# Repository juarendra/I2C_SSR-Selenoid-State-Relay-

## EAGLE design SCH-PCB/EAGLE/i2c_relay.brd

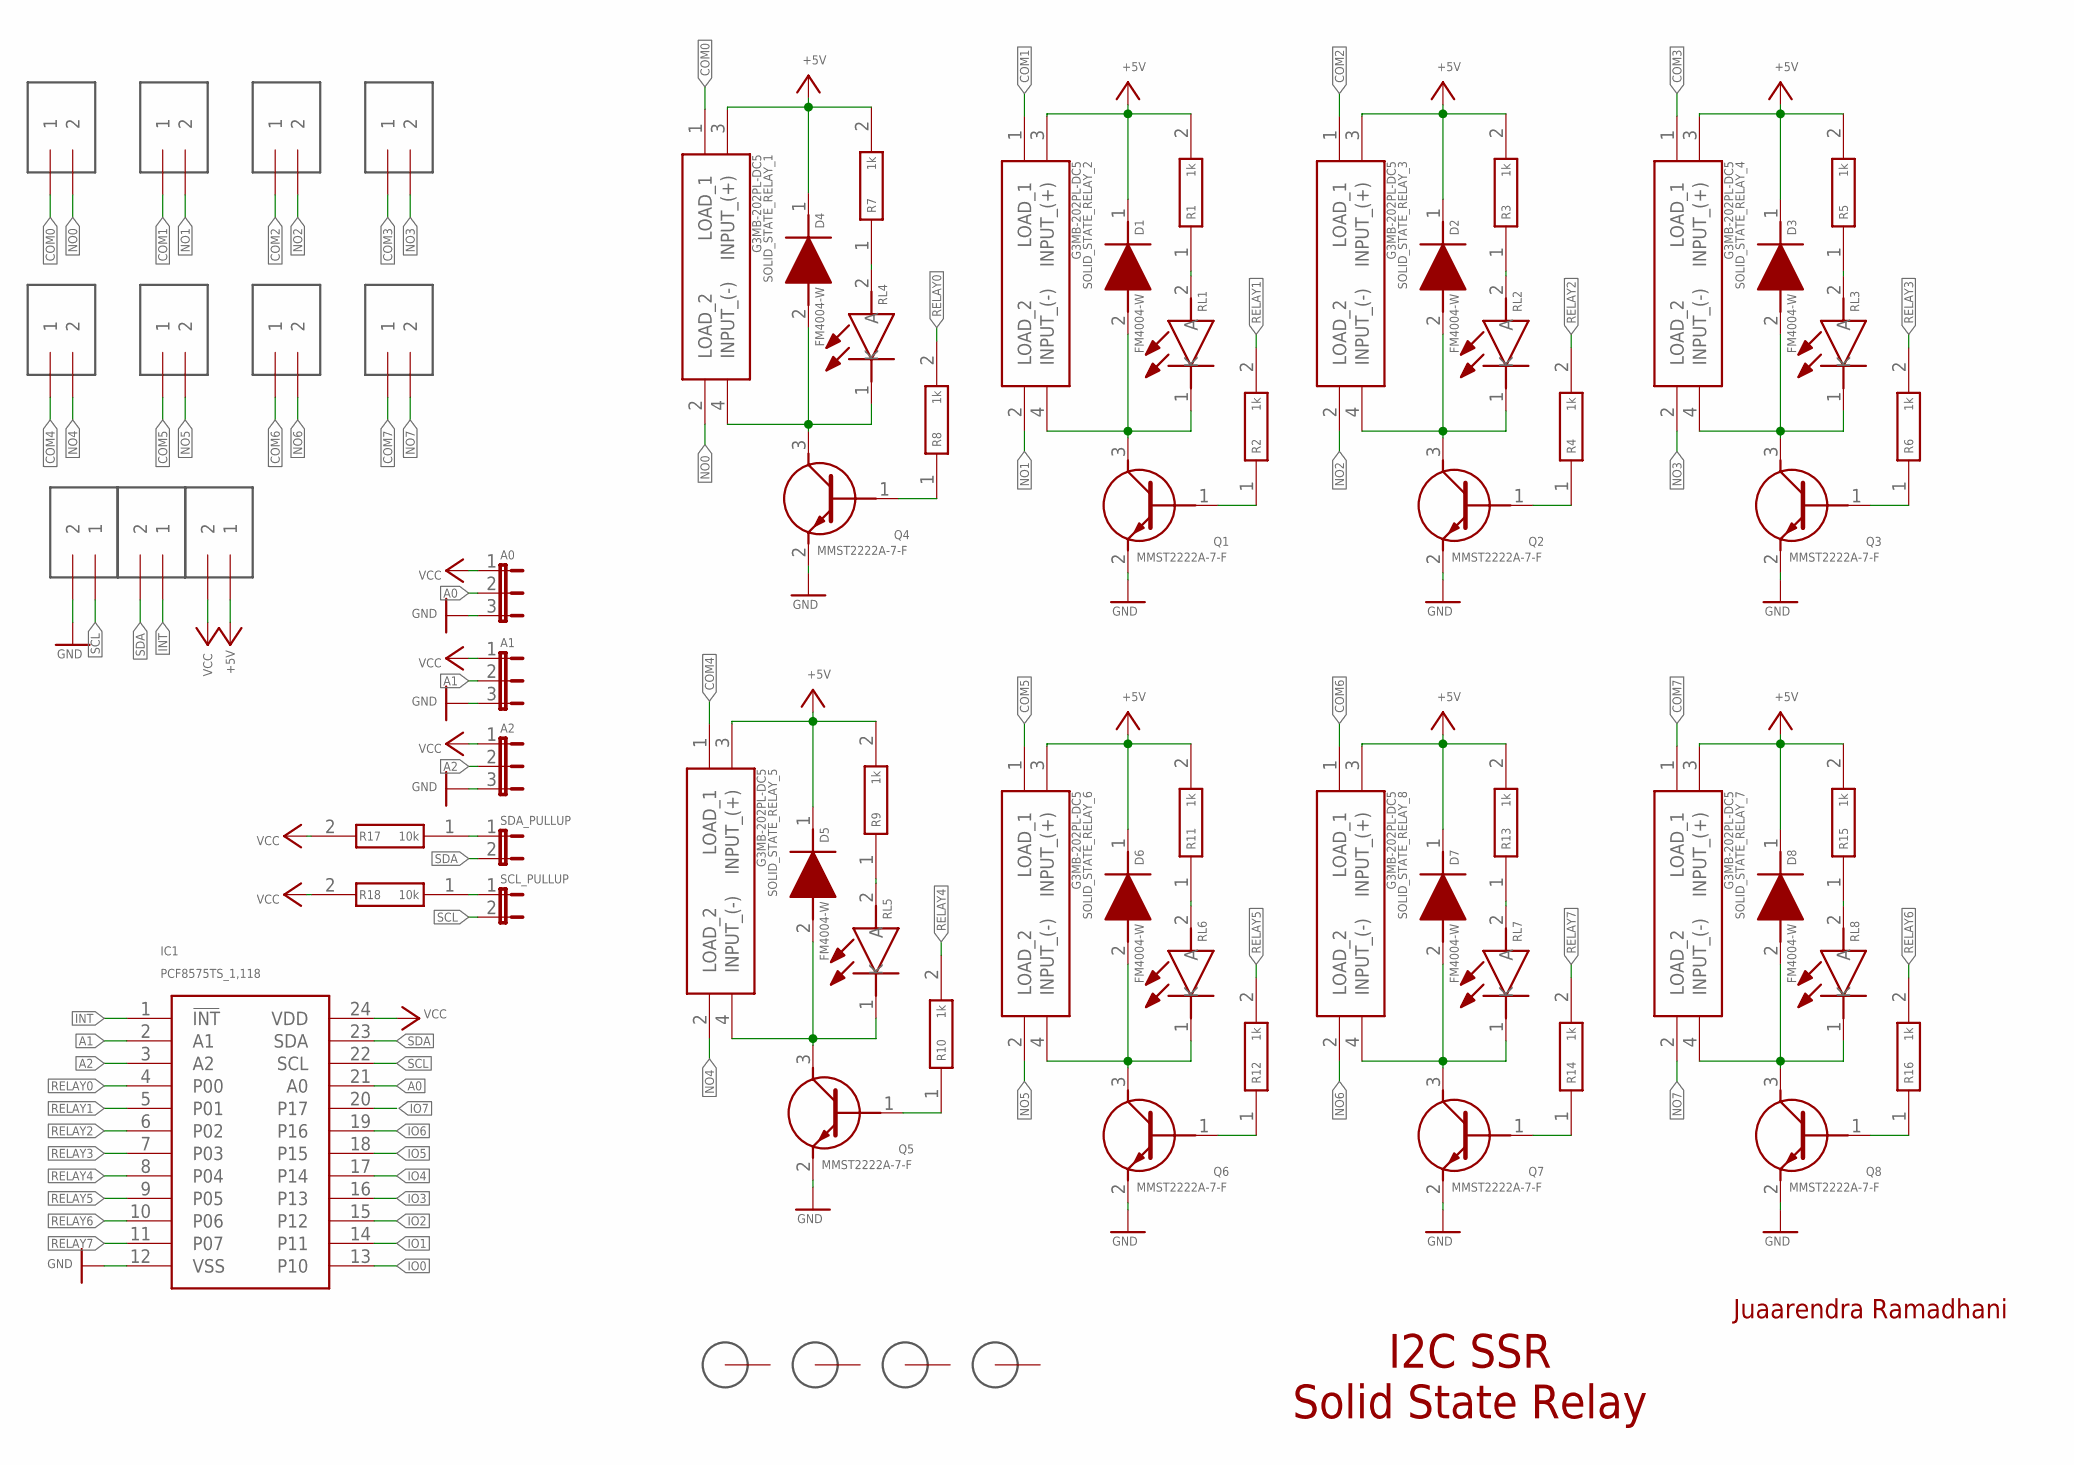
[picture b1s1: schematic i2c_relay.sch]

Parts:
A0, A1, A2: JP2E; JP2
D1, D2, D3, D4, D5, D6, D7, D8: FM4004-W; DIONM5025X231N
H1, H2, H3, H4: 3MM_HOLE
IC1: PCF8575TS_1,118; SOP65P775X200-24N
Q1, Q2, Q3, Q4, Q5, Q6, Q7, Q8: MMST2222A-7-F; SOT65P210X110-3N
R1, R2, R3, R4, R5, R6, R7, R8, R9, R10, R11, R12, R13, R14, R15, R16: 1k; ERA3AEB101V
R17, R18: 10k; RESC1608X55N
RL1, RL2, RL3, RL4, RL5, RL6, RL7, RL8: 150080SS75000; LEDC2012X80N
SCL_PULLUP: JP1E; JP1
SDA_PULLUP: JP1E; JP1
SOLID_STATE_RELAY_1, SOLID_STATE_RELAY_2, SOLID_STATE_RELAY_3, SOLID_STATE_RELAY_4, SOLID_STATE_RELAY_5, SOLID_STATE_RELAY_6, SOLID_STATE_RELAY_7, SOLID_STATE_RELAY_8: G3MB-202PL-DC5; G3MB202PLDC5
U$1, U$2, U$3, U$4, U$5, U$6, U$7, U$8, U$9, U$10, U$11: TERMINAL_2P; KF301-2P

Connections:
+5V: D1.1 (K), D2.1 (K), D3.1 (K), D4.1 (K), D5.1 (K), D6.1 (K), D7.1 (K), D8.1 (K), R1.2, R3.2, R5.2, R7.2, R9.2, R11.2, R13.2, R15.2, SOLID_STATE_RELAY_1.3 (INPUT_(+)), SOLID_STATE_RELAY_2.3 (INPUT_(+)), SOLID_STATE_RELAY_3.3 (INPUT_(+)), SOLID_STATE_RELAY_4.3 (INPUT_(+)), SOLID_STATE_RELAY_5.3 (INPUT_(+)), SOLID_STATE_RELAY_6.3 (INPUT_(+)), SOLID_STATE_RELAY_7.3 (INPUT_(+)), SOLID_STATE_RELAY_8.3 (INPUT_(+)), U$11.1
A0: A0.2, IC1.21 (A0)
A1: A1.2, IC1.2 (A1)
A2: A2.2, IC1.3 (A2)
COM0: SOLID_STATE_RELAY_1.1 (LOAD_1), U$1.1
COM1: SOLID_STATE_RELAY_2.1 (LOAD_1), U$2.1
COM2: SOLID_STATE_RELAY_3.1 (LOAD_1), U$3.1
COM3: SOLID_STATE_RELAY_4.1 (LOAD_1), U$4.1
COM4: SOLID_STATE_RELAY_5.1 (LOAD_1), U$5.1
COM5: SOLID_STATE_RELAY_6.1 (LOAD_1), U$6.1
COM6: SOLID_STATE_RELAY_8.1 (LOAD_1), U$7.1
COM7: SOLID_STATE_RELAY_7.1 (LOAD_1), U$8.1
GND: A0.3, A1.3, A2.3, IC1.12 (VSS), Q1.2 (E), Q2.2 (E), Q3.2 (E), Q4.2 (E), Q5.2 (E), Q6.2 (E), Q7.2 (E), Q8.2 (E), U$9.2
INT: IC1.1 (!INT), U$10.1
IO0: IC1.13 (P10)
IO1: IC1.14 (P11)
IO2: IC1.15 (P12)
IO3: IC1.16 (P13)
IO4: IC1.17 (P14)
IO5: IC1.18 (P15)
IO6: IC1.19 (P16)
IO7: IC1.20 (P17)
unnamed: R1.1, RL1.2 (A)
unnamed: D1.2 (A), Q1.3 (C), RL1.1 (K), SOLID_STATE_RELAY_2.4 (INPUT_(-))
unnamed: Q1.1 (B), R2.1
unnamed: R3.1, RL2.2 (A)
unnamed: D2.2 (A), Q2.3 (C), RL2.1 (K), SOLID_STATE_RELAY_3.4 (INPUT_(-))
unnamed: Q2.1 (B), R4.1
unnamed: R5.1, RL3.2 (A)
unnamed: D3.2 (A), Q3.3 (C), RL3.1 (K), SOLID_STATE_RELAY_4.4 (INPUT_(-))
unnamed: Q3.1 (B), R6.1
unnamed: R7.1, RL4.2 (A)
unnamed: D4.2 (A), Q4.3 (C), RL4.1 (K), SOLID_STATE_RELAY_1.4 (INPUT_(-))
unnamed: Q4.1 (B), R8.1
unnamed: R9.1, RL5.2 (A)
unnamed: D5.2 (A), Q5.3 (C), RL5.1 (K), SOLID_STATE_RELAY_5.4 (INPUT_(-))
unnamed: Q5.1 (B), R10.1
unnamed: R11.1, RL6.2 (A)
unnamed: D6.2 (A), Q6.3 (C), RL6.1 (K), SOLID_STATE_RELAY_6.4 (INPUT_(-))
unnamed: Q6.1 (B), R12.1
unnamed: R13.1, RL7.2 (A)
unnamed: D7.2 (A), Q7.3 (C), RL7.1 (K), SOLID_STATE_RELAY_8.4 (INPUT_(-))
unnamed: Q7.1 (B), R14.1
unnamed: R15.1, RL8.2 (A)
unnamed: D8.2 (A), Q8.3 (C), RL8.1 (K), SOLID_STATE_RELAY_7.4 (INPUT_(-))
unnamed: Q8.1 (B), R16.1
unnamed: R17.1, SDA_PULLUP.1
unnamed: R18.1, SCL_PULLUP.1
NO0: SOLID_STATE_RELAY_1.2 (LOAD_2), U$1.2
NO1: SOLID_STATE_RELAY_2.2 (LOAD_2), U$2.2
NO2: SOLID_STATE_RELAY_3.2 (LOAD_2), U$3.2
NO3: SOLID_STATE_RELAY_4.2 (LOAD_2), U$4.2
NO4: SOLID_STATE_RELAY_5.2 (LOAD_2), U$5.2
NO5: SOLID_STATE_RELAY_6.2 (LOAD_2), U$6.2
NO6: SOLID_STATE_RELAY_8.2 (LOAD_2), U$7.2
NO7: SOLID_STATE_RELAY_7.2 (LOAD_2), U$8.2
RELAY0: IC1.4 (P00), R8.2
RELAY1: IC1.5 (P01), R2.2
RELAY2: IC1.6 (P02), R4.2
RELAY3: IC1.7 (P03), R6.2
RELAY4: IC1.8 (P04), R10.2
RELAY5: IC1.9 (P05), R12.2
RELAY6: IC1.10 (P06), R16.2
RELAY7: IC1.11 (P07), R14.2
SCL: IC1.22 (SCL), SCL_PULLUP.2, U$9.1
SDA: IC1.23 (SDA), SDA_PULLUP.2, U$10.2
VCC: A0.1, A1.1, A2.1, IC1.24 (VDD), R17.2, R18.2, U$11.2

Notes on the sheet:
I2C SSR Solid State Relay
Juaarendra Ramadhani

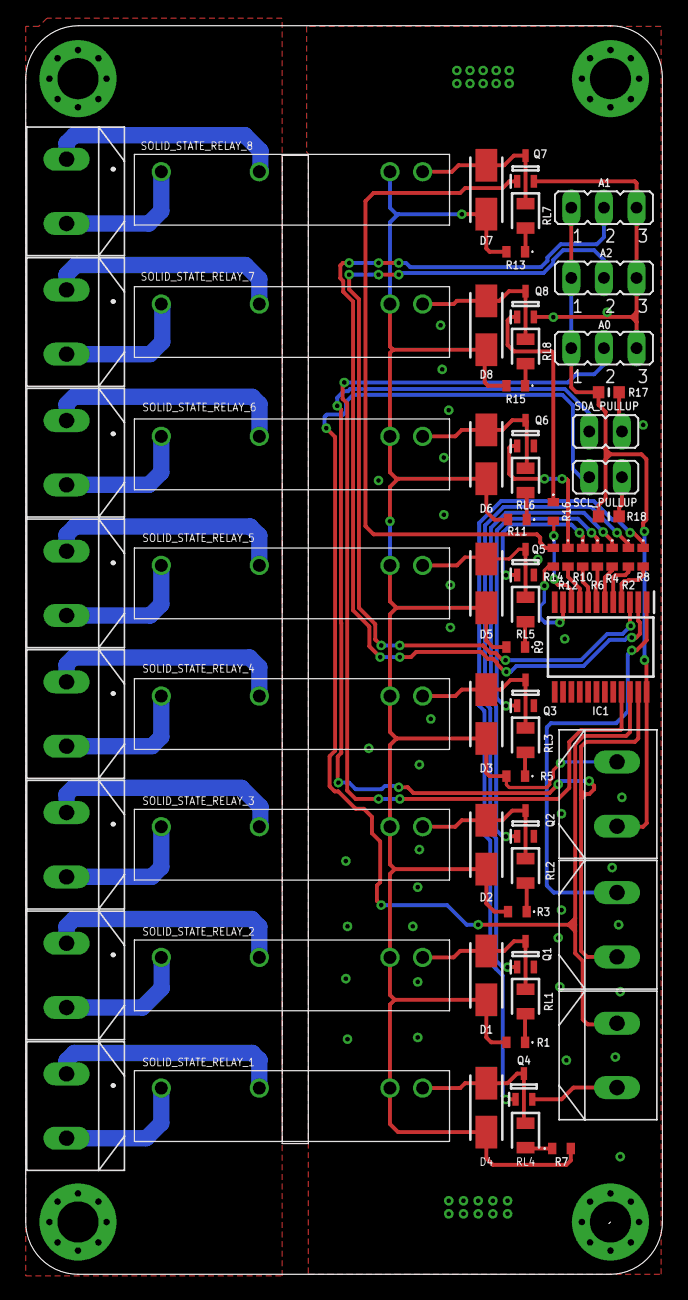
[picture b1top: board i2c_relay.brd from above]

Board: 2 copper layers, 49.4 x 97.0 mm, 71 parts (0 on the bottom side), 59 nets.

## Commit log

2024-07-21 FEAT: add board pcb
2024-07-21 FEAT: add 3d and push to FUSION360
2024-07-21 FEAT: change folder
2024-07-21 FEAT: add pdf schematic
2024-07-21 FEAT: add gerber
2024-07-22 FEAT: update silkscreen board pcb
2024-07-22 FEAT: update gerber
2024-07-22 FEAT: add 3d model, dimension and preview hardware
2024-07-23 FEAT: update pinout
2024-07-23 DOC: add pinout on readme
2024-07-24 FEAT: add firmare example
